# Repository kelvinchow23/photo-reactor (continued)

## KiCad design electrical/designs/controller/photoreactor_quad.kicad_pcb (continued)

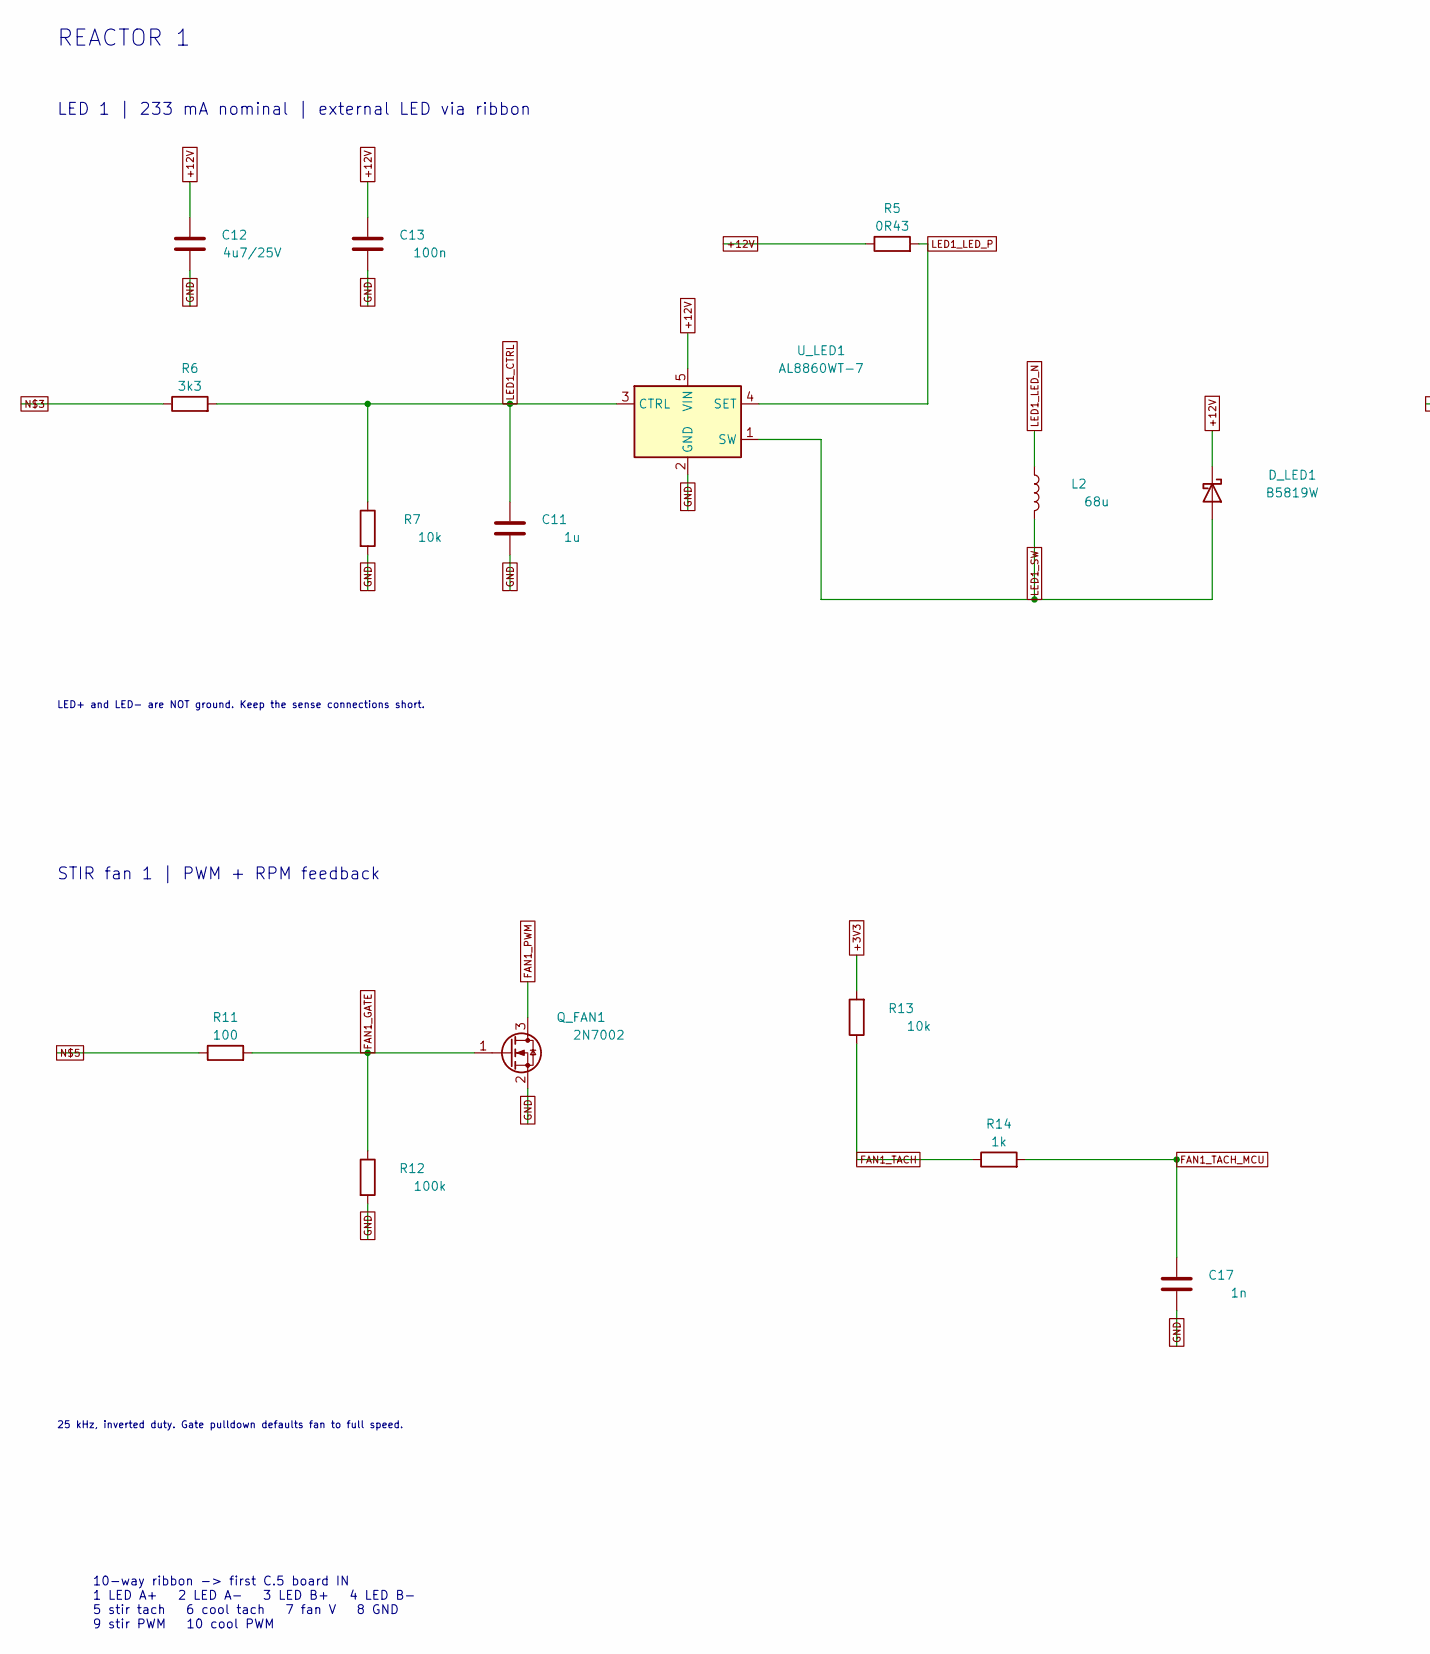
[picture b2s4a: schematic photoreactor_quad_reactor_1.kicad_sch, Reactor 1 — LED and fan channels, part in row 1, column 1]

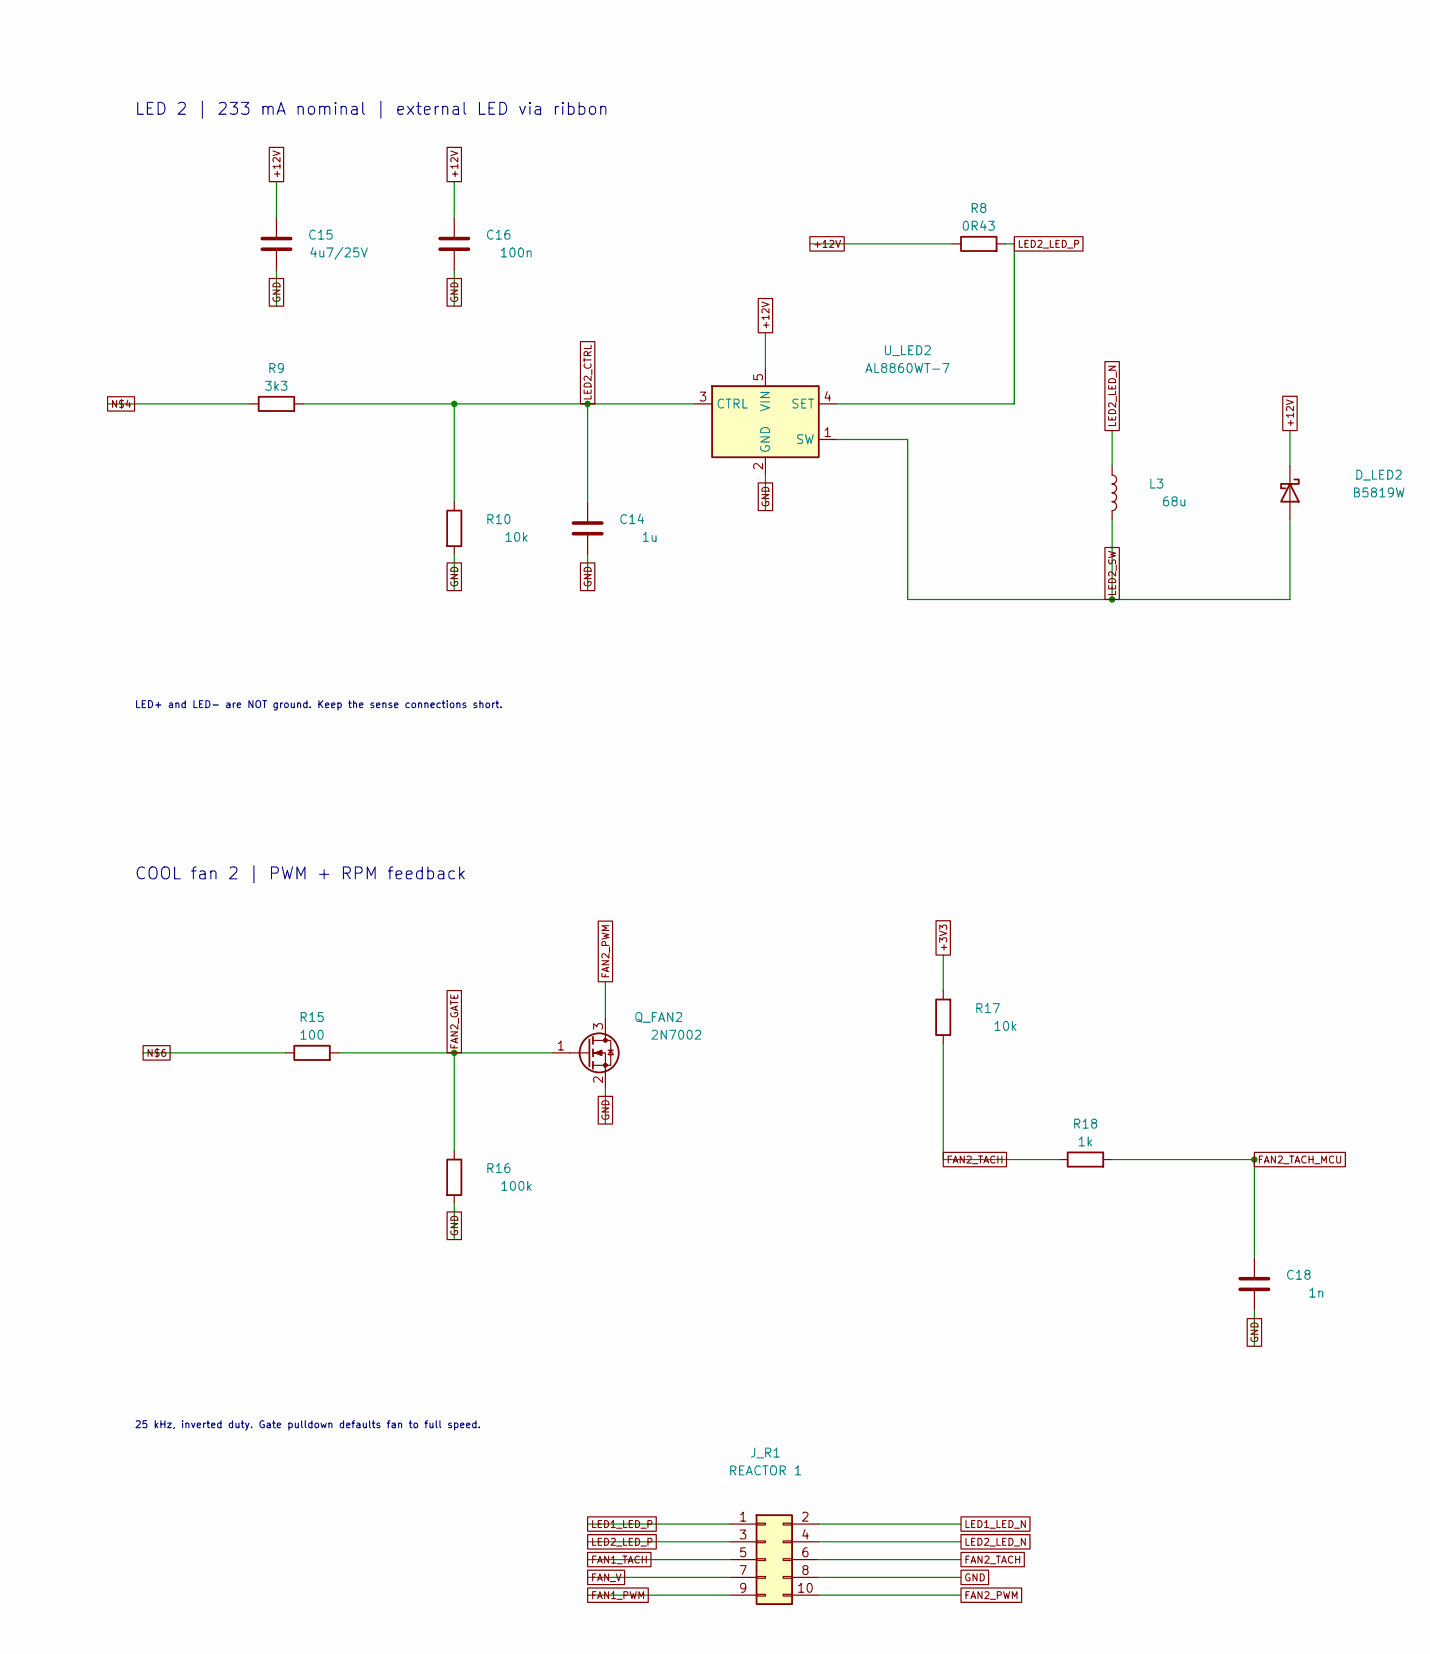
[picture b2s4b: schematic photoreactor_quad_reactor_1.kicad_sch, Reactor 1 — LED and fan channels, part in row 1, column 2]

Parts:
C11, C14: 1u; C_0805_2012Metric; MPN CL21B105KBFNNNE; LCSC C28323
C12, C15: 4u7/25V; C_0805_2012Metric; MPN CL21A475KAQNNNE; LCSC C1779
C13, C16: 100n; C_0805_2012Metric; MPN CC0805KRX7R9BB104; LCSC C49678
C17, C18: 1n; C_0805_2012Metric; MPN CL21B102KCANNNC; LCSC C15177
D_LED1, D_LED2: B5819W; D_SOD-123; MPN B5819W SL
J_R1: REACTOR 1; JXT_IDC2.54_2X5P_A2; MPN JXT-IDC2.54-2X5P-A2
L2, L3: 68u; L_Bourns_SRN6045TA; MPN SRN6045TA-680M
Q_FAN1, Q_FAN2: 2N7002; SOT-23; MPN 2N7002
R5, R8: 0R43; R_1206_3216Metric; MPN CR1206FR430P05R
R6, R9: 3k3; R_0805_2012Metric; MPN 0805W8F3301T5E; LCSC C26010
R7, R10, R13, R17: 10k; R_0805_2012Metric; MPN 0805W8F1002T5E; LCSC C17414
R11, R15: 100; R_0805_2012Metric; MPN 0805W8F1000T5E; LCSC C17408
R12, R16: 100k; R_0805_2012Metric; MPN 0805W8F1003T5E; LCSC C149504
R14, R18: 1k; R_0805_2012Metric; MPN 0805W8F1001T5E; LCSC C17513
U_LED1, U_LED2: AL8860WT-7; SOT-23-5; MPN AL8860WT-7

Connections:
+3V3: R13.2, R17.2; also elsewhere on the board
+12V: C12.1, C13.1, C15.1, C16.1, D_LED1.1 (K), D_LED2.1 (K), R5.1, R8.1, U_LED1.5 (VIN), U_LED2.5 (VIN); also elsewhere on the board
FAN1_GATE: Q_FAN1.1 (G), R11.2, R12.1
FAN1_PWM: J_R1.9, Q_FAN1.3 (D)
FAN1_TACH: J_R1.5, R13.1, R14.1
FAN1_TACH_MCU: C17.1, R14.2; also elsewhere on the board
FAN2_GATE: Q_FAN2.1 (G), R15.2, R16.1
FAN2_PWM: J_R1.10, Q_FAN2.3 (D)
FAN2_TACH: J_R1.6, R17.1, R18.1
FAN2_TACH_MCU: C18.1, R18.2; also elsewhere on the board
FAN_V: J_R1.7; also elsewhere on the board
GND: C11.2, C12.2, C13.2, C14.2, C15.2, C16.2, C17.2, C18.2, J_R1.8, Q_FAN1.2 (S), Q_FAN2.2 (S), R7.2, R10.2, R12.2, R16.2, U_LED1.2 (GND), U_LED2.2 (GND); also elsewhere on the board
LED1_CTRL: C11.1, R6.2, R7.1, U_LED1.3 (CTRL)
LED1_LED_N: J_R1.2, L2.1
LED1_LED_P: J_R1.1, R5.2, U_LED1.4 (SET)
LED1_SW: D_LED1.2 (A), L2.2, U_LED1.1 (SW)
LED2_CTRL: C14.1, R9.2, R10.1, U_LED2.3 (CTRL)
LED2_LED_N: J_R1.4, L3.1
LED2_LED_P: J_R1.3, R8.2, U_LED2.4 (SET)
LED2_SW: D_LED2.2 (A), L3.2, U_LED2.1 (SW)
unnamed 73: R6.1; also elsewhere on the board
unnamed 74: R9.1; also elsewhere on the board
unnamed 75: R11.1; also elsewhere on the board
unnamed 76: R15.1; also elsewhere on the board

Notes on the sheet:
REACTOR 1
LED 1 | 233 mA nominal | external LED via ribbon
LED+ and LED- are NOT ground. Keep the sense connections short.
LED 2 | 233 mA nominal | external LED via ribbon
STIR fan 1 | PWM + RPM feedback
25 kHz, inverted duty. Gate pulldown defaults fan to full speed.
COOL fan 2 | PWM + RPM feedback
10-way ribbon -> first C.5 board IN 1 LED A+ 2 LED A- 3 LED B+ 4 LED B- 5 stir tach 6 cool tach 7 fan V 8 GND 9 stir PWM 10 cool PWM

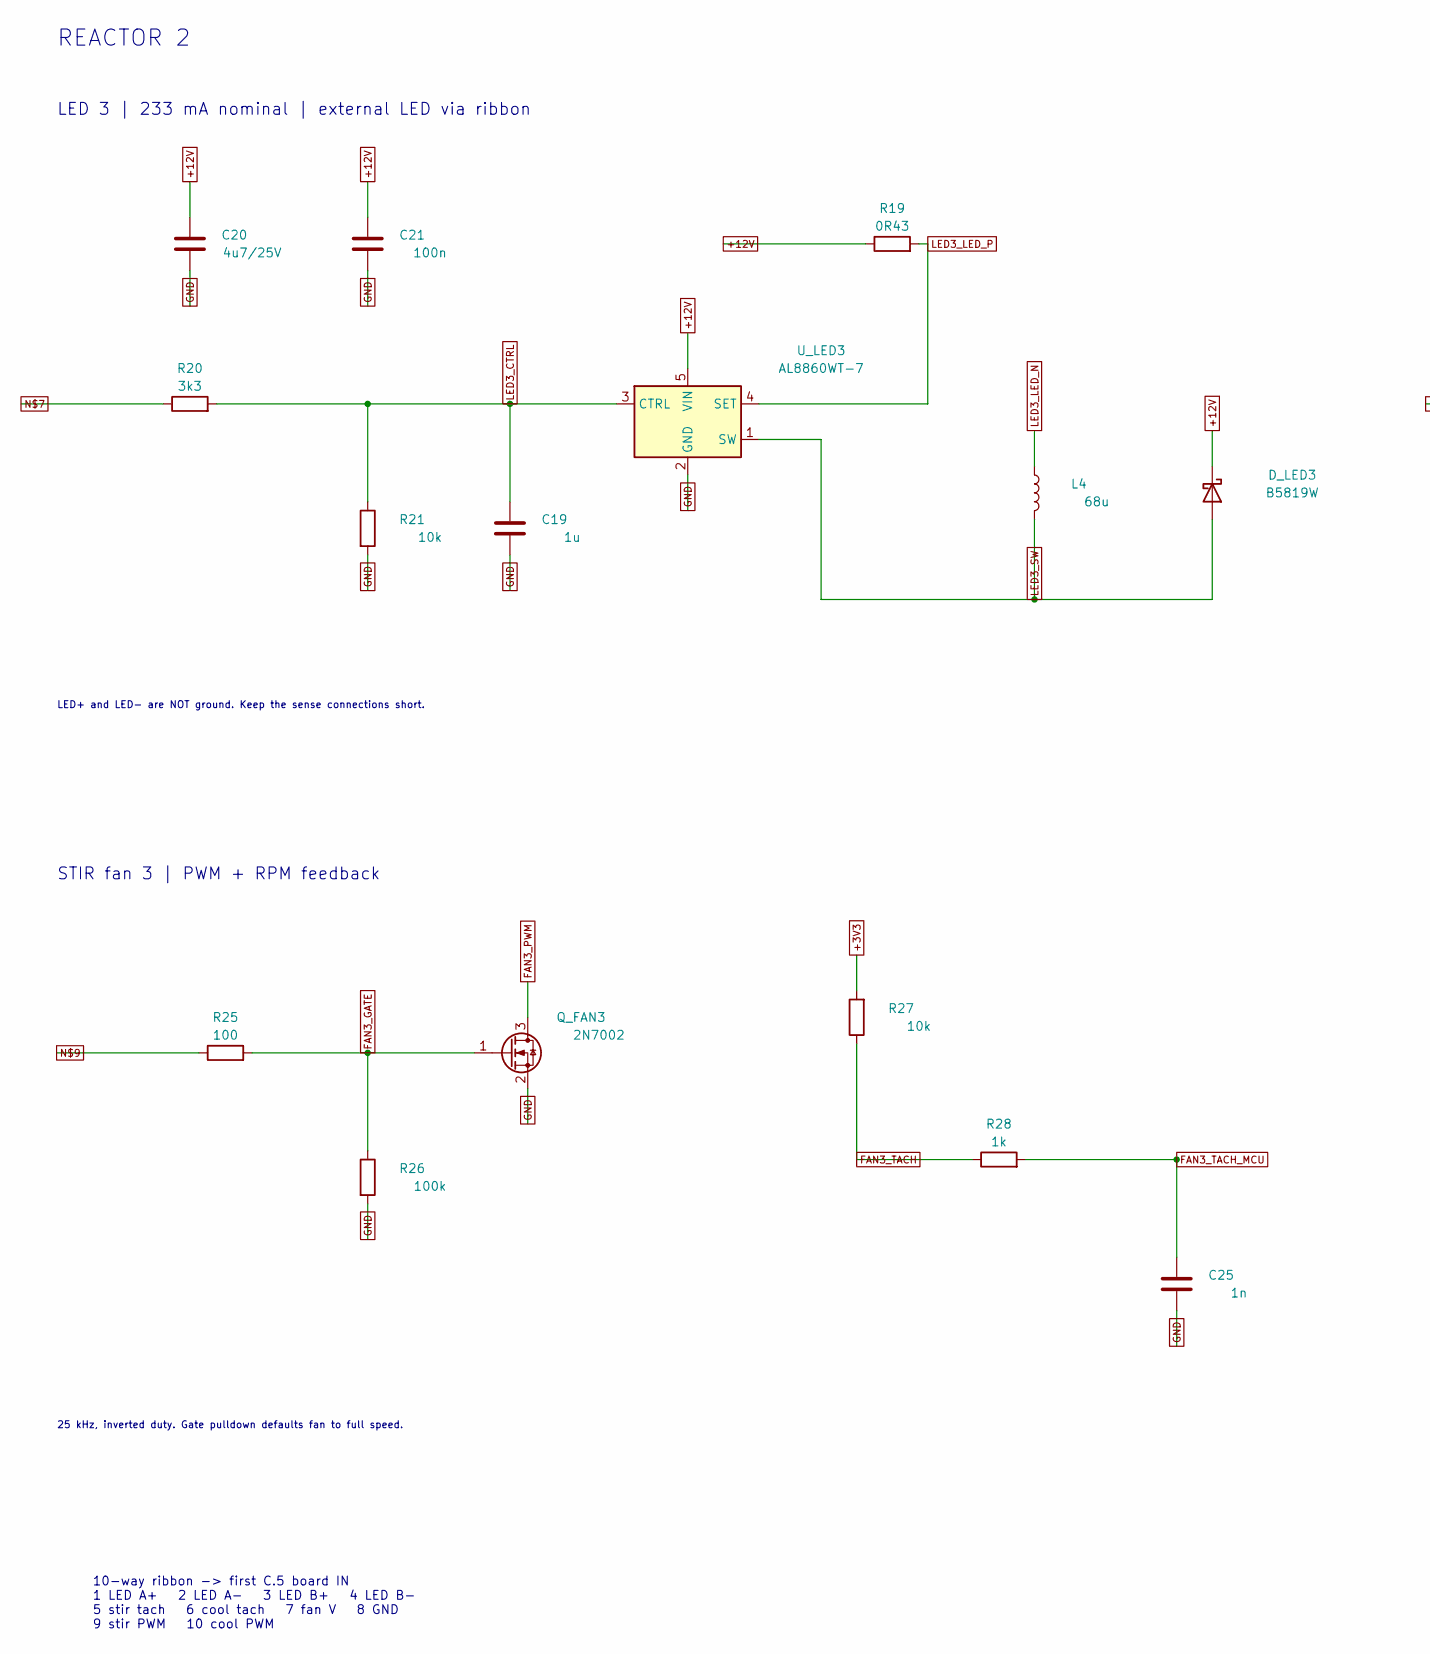
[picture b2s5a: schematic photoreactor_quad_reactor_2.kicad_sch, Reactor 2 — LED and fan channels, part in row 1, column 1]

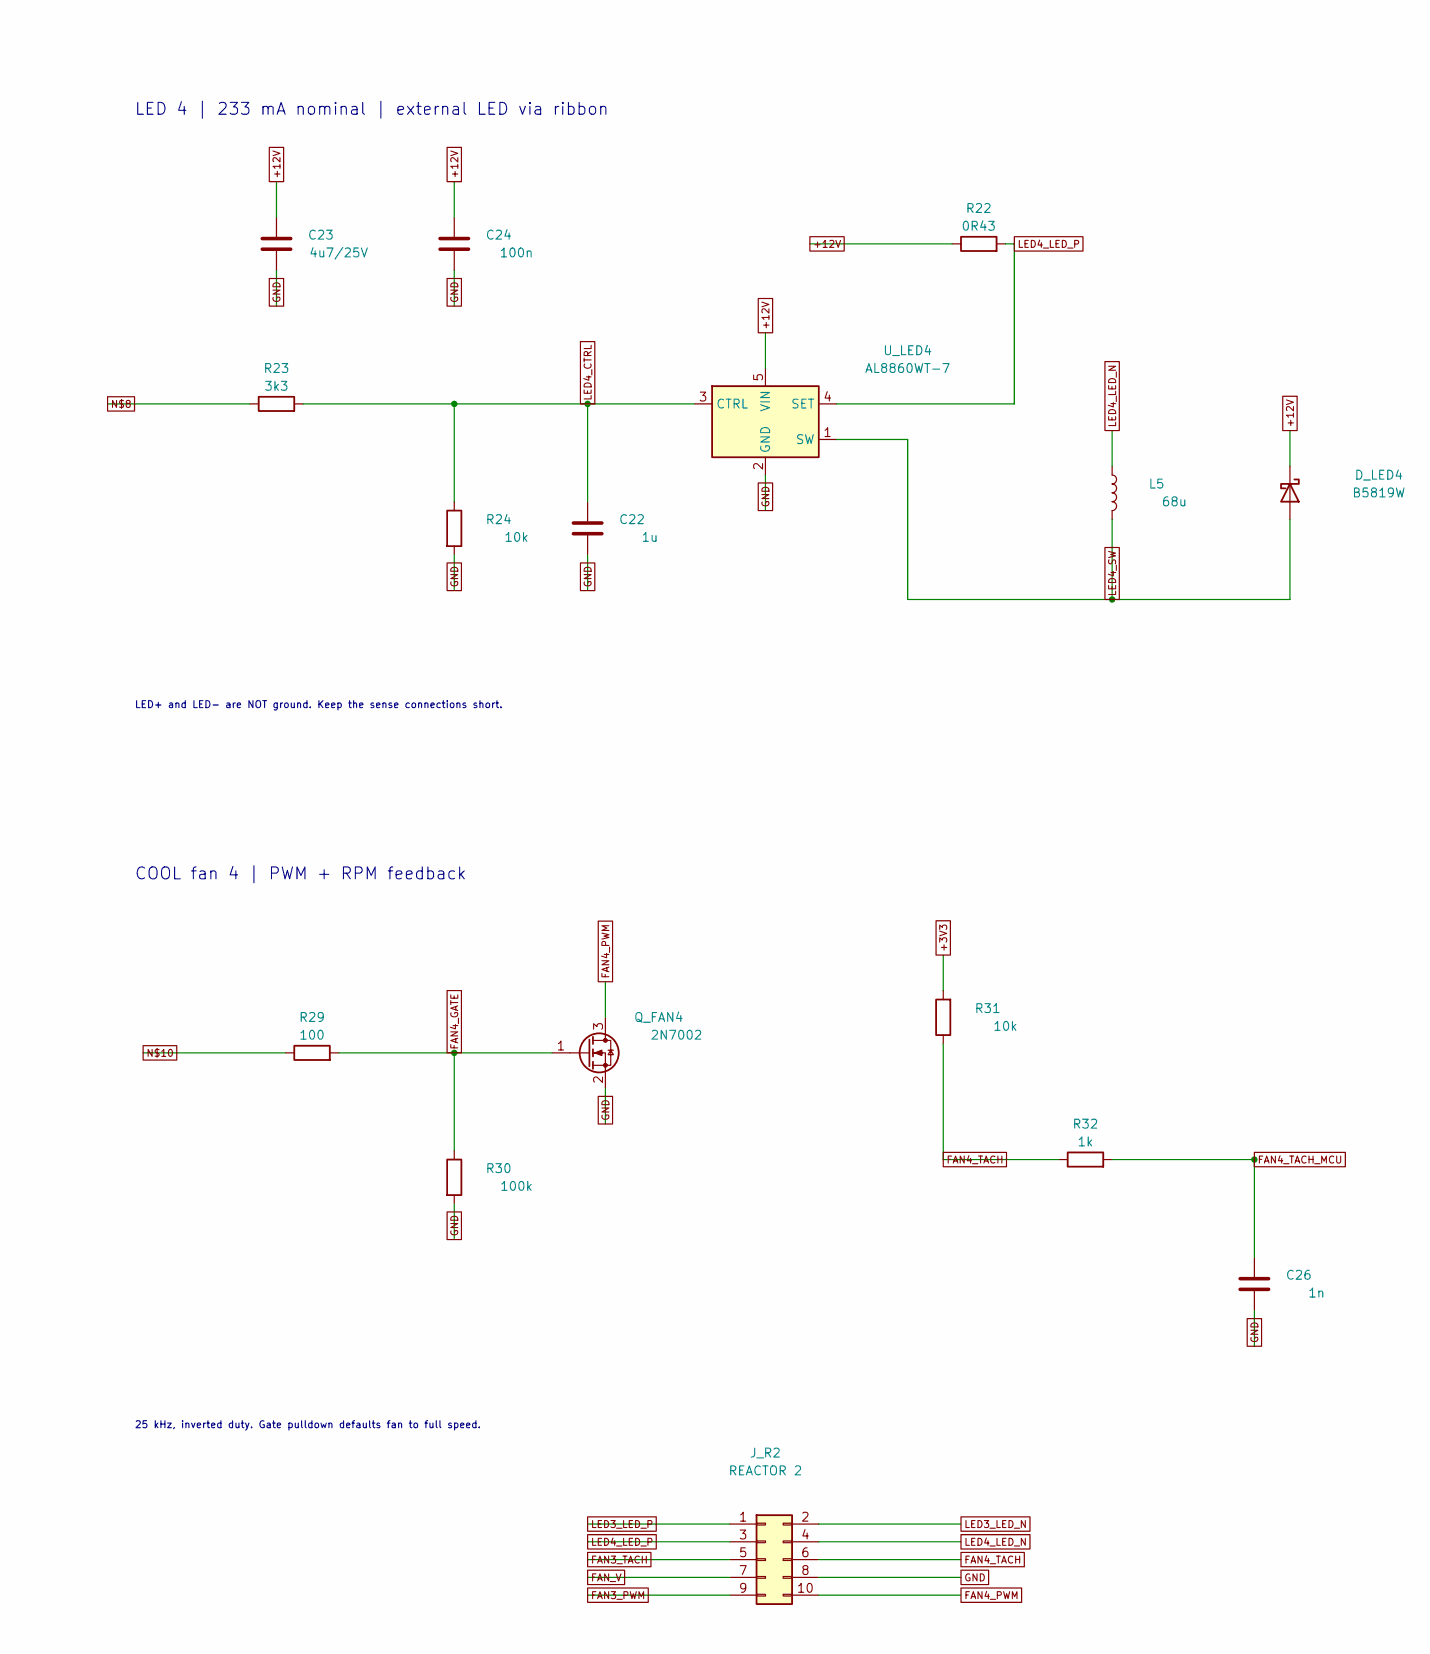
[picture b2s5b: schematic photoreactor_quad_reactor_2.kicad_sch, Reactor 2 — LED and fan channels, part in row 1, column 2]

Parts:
C19, C22: 1u; C_0805_2012Metric; MPN CL21B105KBFNNNE; LCSC C28323
C20, C23: 4u7/25V; C_0805_2012Metric; MPN CL21A475KAQNNNE; LCSC C1779
C21, C24: 100n; C_0805_2012Metric; MPN CC0805KRX7R9BB104; LCSC C49678
C25, C26: 1n; C_0805_2012Metric; MPN CL21B102KCANNNC; LCSC C15177
D_LED3, D_LED4: B5819W; D_SOD-123; MPN B5819W SL
J_R2: REACTOR 2; JXT_IDC2.54_2X5P_A2; MPN JXT-IDC2.54-2X5P-A2
L4, L5: 68u; L_Bourns_SRN6045TA; MPN SRN6045TA-680M
Q_FAN3, Q_FAN4: 2N7002; SOT-23; MPN 2N7002
R19, R22: 0R43; R_1206_3216Metric; MPN CR1206FR430P05R
R20, R23: 3k3; R_0805_2012Metric; MPN 0805W8F3301T5E; LCSC C26010
R21, R24, R27, R31: 10k; R_0805_2012Metric; MPN 0805W8F1002T5E; LCSC C17414
R25, R29: 100; R_0805_2012Metric; MPN 0805W8F1000T5E; LCSC C17408
R26, R30: 100k; R_0805_2012Metric; MPN 0805W8F1003T5E; LCSC C149504
R28, R32: 1k; R_0805_2012Metric; MPN 0805W8F1001T5E; LCSC C17513
U_LED3, U_LED4: AL8860WT-7; SOT-23-5; MPN AL8860WT-7

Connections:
+3V3: R27.2, R31.2; also elsewhere on the board
+12V: C20.1, C21.1, C23.1, C24.1, D_LED3.1 (K), D_LED4.1 (K), R19.1, R22.1, U_LED3.5 (VIN), U_LED4.5 (VIN); also elsewhere on the board
FAN3_GATE: Q_FAN3.1 (G), R25.2, R26.1
FAN3_PWM: J_R2.9, Q_FAN3.3 (D)
FAN3_TACH: J_R2.5, R27.1, R28.1
FAN3_TACH_MCU: C25.1, R28.2; also elsewhere on the board
FAN4_GATE: Q_FAN4.1 (G), R29.2, R30.1
FAN4_PWM: J_R2.10, Q_FAN4.3 (D)
FAN4_TACH: J_R2.6, R31.1, R32.1
FAN4_TACH_MCU: C26.1, R32.2; also elsewhere on the board
FAN_V: J_R2.7; also elsewhere on the board
GND: C19.2, C20.2, C21.2, C22.2, C23.2, C24.2, C25.2, C26.2, J_R2.8, Q_FAN3.2 (S), Q_FAN4.2 (S), R21.2, R24.2, R26.2, R30.2, U_LED3.2 (GND), U_LED4.2 (GND); also elsewhere on the board
LED3_CTRL: C19.1, R20.2, R21.1, U_LED3.3 (CTRL)
LED3_LED_N: J_R2.2, L4.1
LED3_LED_P: J_R2.1, R19.2, U_LED3.4 (SET)
LED3_SW: D_LED3.2 (A), L4.2, U_LED3.1 (SW)
LED4_CTRL: C22.1, R23.2, R24.1, U_LED4.3 (CTRL)
LED4_LED_N: J_R2.4, L5.1
LED4_LED_P: J_R2.3, R22.2, U_LED4.4 (SET)
LED4_SW: D_LED4.2 (A), L5.2, U_LED4.1 (SW)
unnamed 77: R20.1; also elsewhere on the board
unnamed 78: R23.1; also elsewhere on the board
unnamed 79: R25.1; also elsewhere on the board
unnamed 80: R29.1; also elsewhere on the board

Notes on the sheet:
REACTOR 2
LED 3 | 233 mA nominal | external LED via ribbon
LED+ and LED- are NOT ground. Keep the sense connections short.
LED 4 | 233 mA nominal | external LED via ribbon
STIR fan 3 | PWM + RPM feedback
25 kHz, inverted duty. Gate pulldown defaults fan to full speed.
COOL fan 4 | PWM + RPM feedback
10-way ribbon -> first C.5 board IN 1 LED A+ 2 LED A- 3 LED B+ 4 LED B- 5 stir tach 6 cool tach 7 fan V 8 GND 9 stir PWM 10 cool PWM

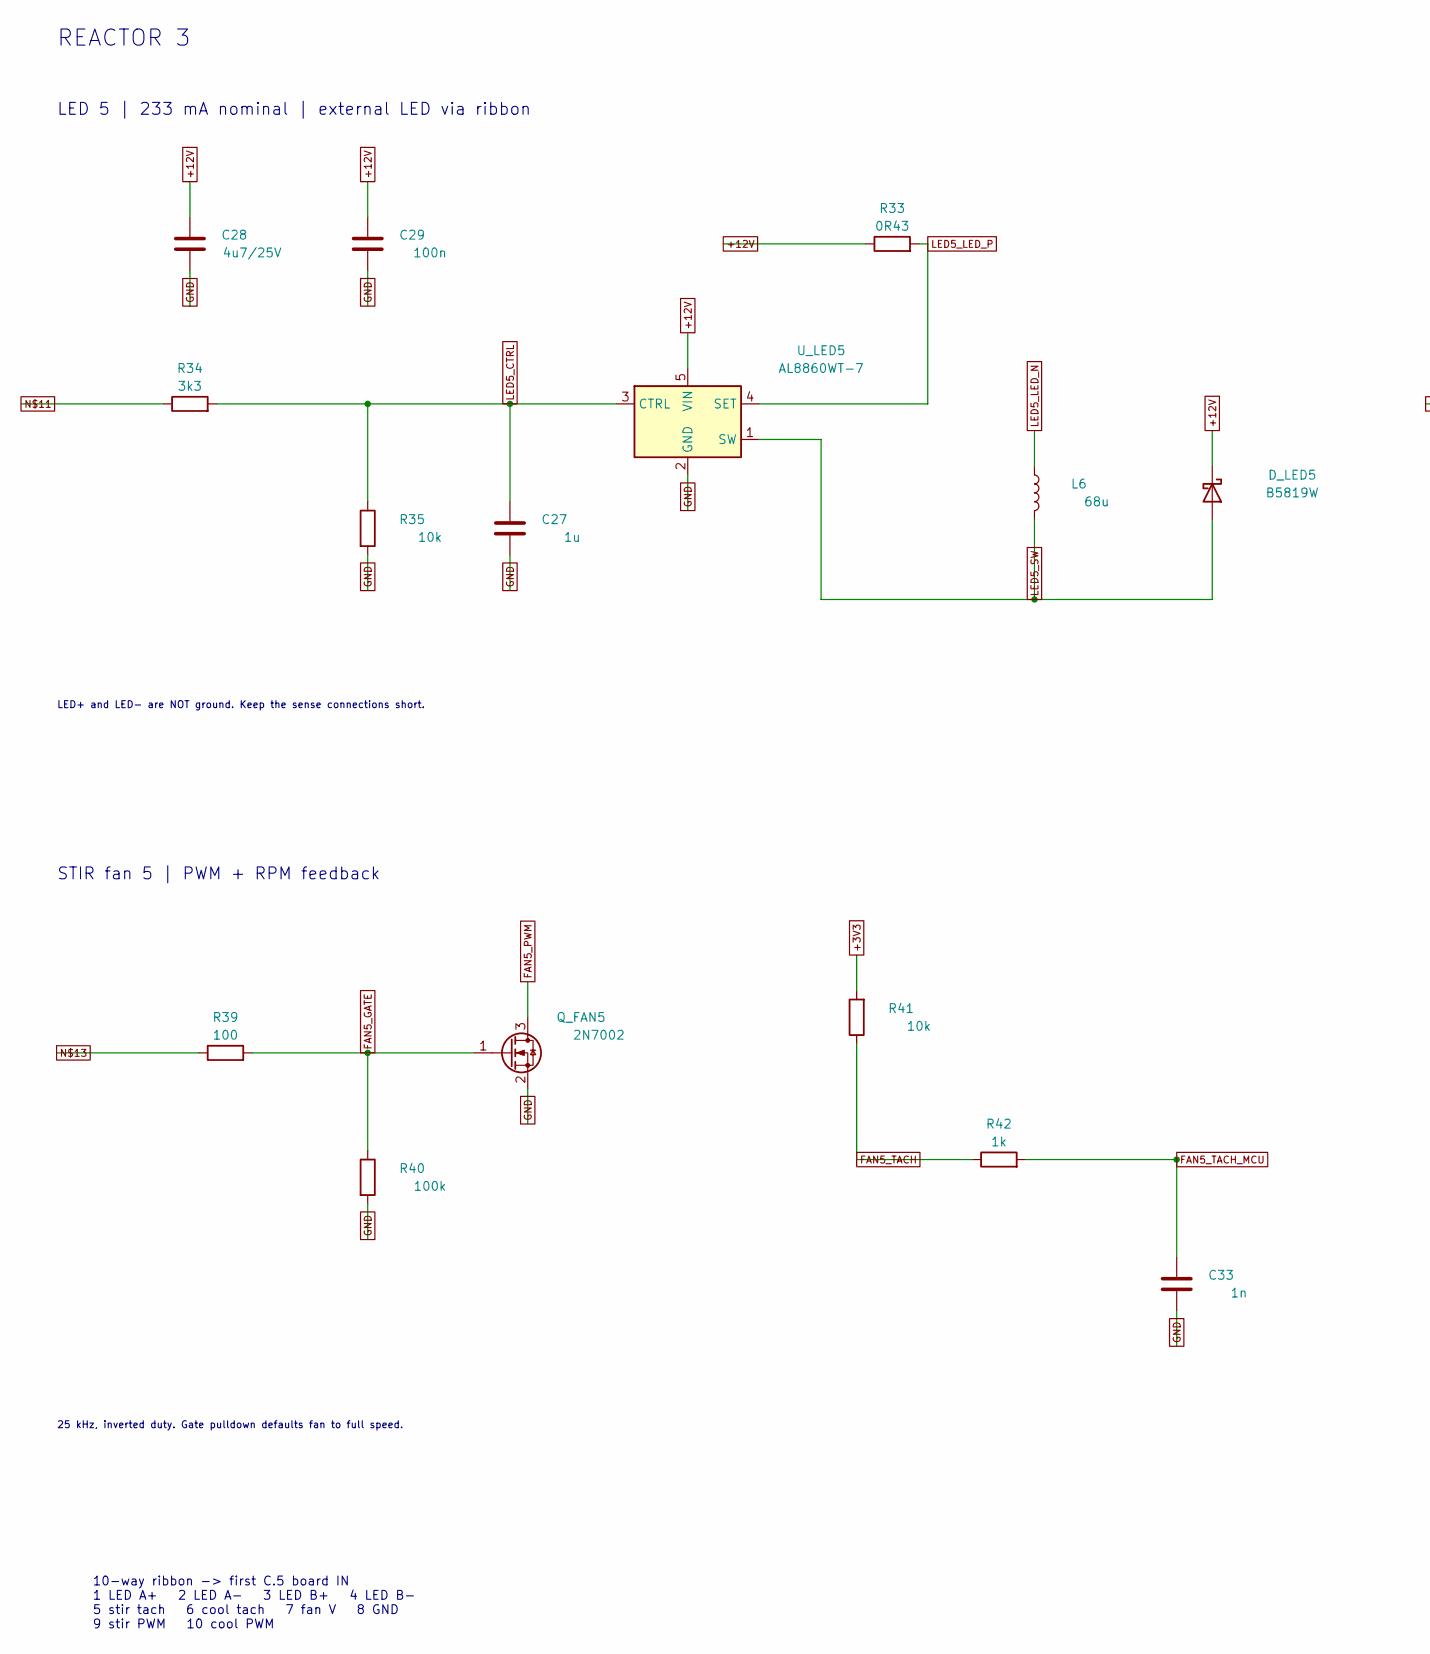
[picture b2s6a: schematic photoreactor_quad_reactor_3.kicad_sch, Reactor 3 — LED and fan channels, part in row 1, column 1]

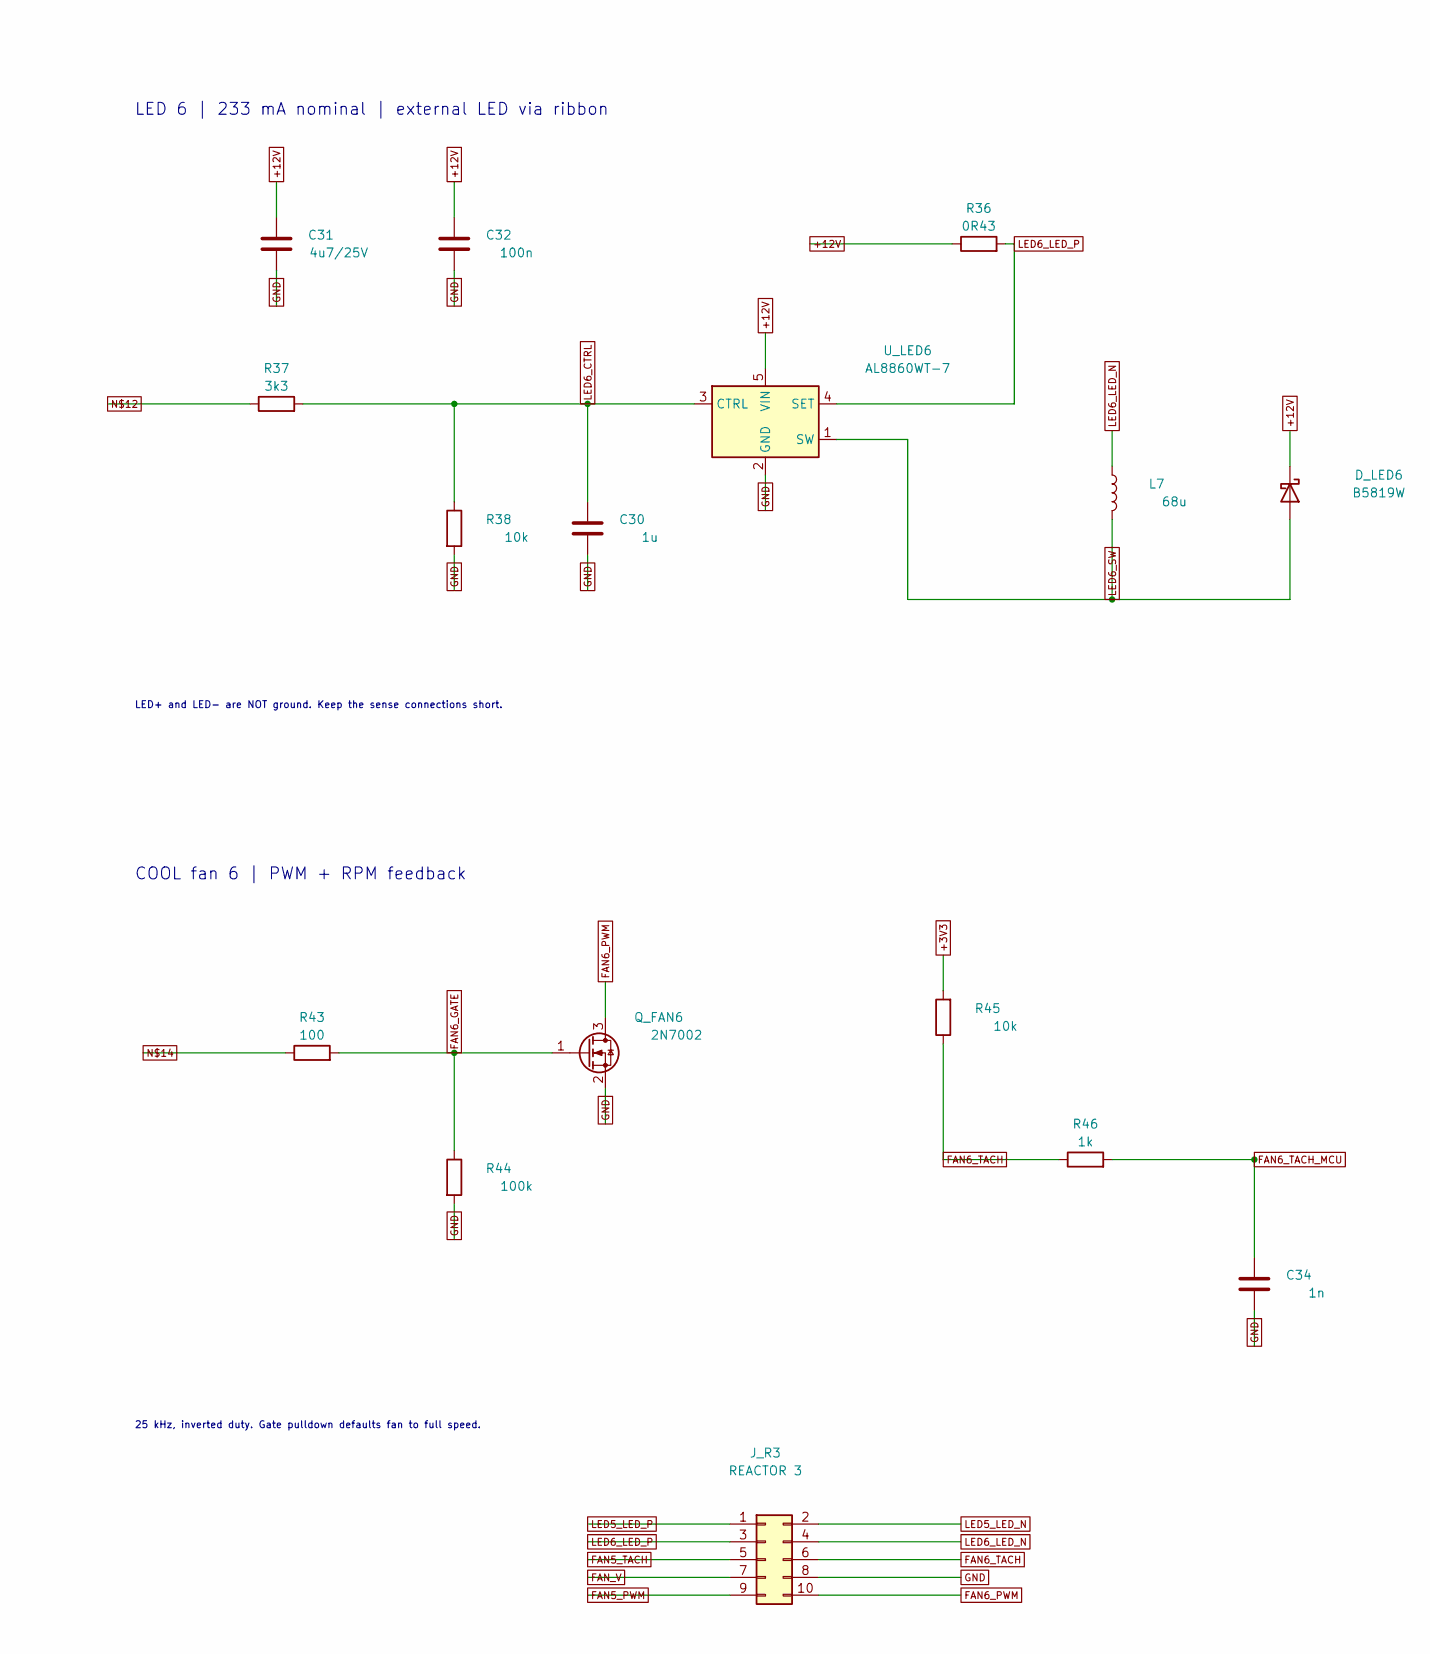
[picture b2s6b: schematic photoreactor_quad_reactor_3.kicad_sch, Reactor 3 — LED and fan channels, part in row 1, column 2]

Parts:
C27, C30: 1u; C_0805_2012Metric; MPN CL21B105KBFNNNE; LCSC C28323
C28, C31: 4u7/25V; C_0805_2012Metric; MPN CL21A475KAQNNNE; LCSC C1779
C29, C32: 100n; C_0805_2012Metric; MPN CC0805KRX7R9BB104; LCSC C49678
C33, C34: 1n; C_0805_2012Metric; MPN CL21B102KCANNNC; LCSC C15177
D_LED5, D_LED6: B5819W; D_SOD-123; MPN B5819W SL
J_R3: REACTOR 3; JXT_IDC2.54_2X5P_A2; MPN JXT-IDC2.54-2X5P-A2
L6, L7: 68u; L_Bourns_SRN6045TA; MPN SRN6045TA-680M
Q_FAN5, Q_FAN6: 2N7002; SOT-23; MPN 2N7002
R33, R36: 0R43; R_1206_3216Metric; MPN CR1206FR430P05R
R34, R37: 3k3; R_0805_2012Metric; MPN 0805W8F3301T5E; LCSC C26010
R35, R38, R41, R45: 10k; R_0805_2012Metric; MPN 0805W8F1002T5E; LCSC C17414
R39, R43: 100; R_0805_2012Metric; MPN 0805W8F1000T5E; LCSC C17408
R40, R44: 100k; R_0805_2012Metric; MPN 0805W8F1003T5E; LCSC C149504
R42, R46: 1k; R_0805_2012Metric; MPN 0805W8F1001T5E; LCSC C17513
U_LED5, U_LED6: AL8860WT-7; SOT-23-5; MPN AL8860WT-7

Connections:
+3V3: R41.2, R45.2; also elsewhere on the board
+12V: C28.1, C29.1, C31.1, C32.1, D_LED5.1 (K), D_LED6.1 (K), R33.1, R36.1, U_LED5.5 (VIN), U_LED6.5 (VIN); also elsewhere on the board
FAN5_GATE: Q_FAN5.1 (G), R39.2, R40.1
FAN5_PWM: J_R3.9, Q_FAN5.3 (D)
FAN5_TACH: J_R3.5, R41.1, R42.1
FAN5_TACH_MCU: C33.1, R42.2; also elsewhere on the board
FAN6_GATE: Q_FAN6.1 (G), R43.2, R44.1
FAN6_PWM: J_R3.10, Q_FAN6.3 (D)
FAN6_TACH: J_R3.6, R45.1, R46.1
FAN6_TACH_MCU: C34.1, R46.2; also elsewhere on the board
FAN_V: J_R3.7; also elsewhere on the board
GND: C27.2, C28.2, C29.2, C30.2, C31.2, C32.2, C33.2, C34.2, J_R3.8, Q_FAN5.2 (S), Q_FAN6.2 (S), R35.2, R38.2, R40.2, R44.2, U_LED5.2 (GND), U_LED6.2 (GND); also elsewhere on the board
LED5_CTRL: C27.1, R34.2, R35.1, U_LED5.3 (CTRL)
LED5_LED_N: J_R3.2, L6.1
LED5_LED_P: J_R3.1, R33.2, U_LED5.4 (SET)
LED5_SW: D_LED5.2 (A), L6.2, U_LED5.1 (SW)
LED6_CTRL: C30.1, R37.2, R38.1, U_LED6.3 (CTRL)
LED6_LED_N: J_R3.4, L7.1
LED6_LED_P: J_R3.3, R36.2, U_LED6.4 (SET)
LED6_SW: D_LED6.2 (A), L7.2, U_LED6.1 (SW)
unnamed 81: R34.1; also elsewhere on the board
unnamed 82: R37.1; also elsewhere on the board
unnamed 83: R39.1; also elsewhere on the board
unnamed 84: R43.1; also elsewhere on the board

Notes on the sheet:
REACTOR 3
LED 5 | 233 mA nominal | external LED via ribbon
LED+ and LED- are NOT ground. Keep the sense connections short.
LED 6 | 233 mA nominal | external LED via ribbon
STIR fan 5 | PWM + RPM feedback
25 kHz, inverted duty. Gate pulldown defaults fan to full speed.
COOL fan 6 | PWM + RPM feedback
10-way ribbon -> first C.5 board IN 1 LED A+ 2 LED A- 3 LED B+ 4 LED B- 5 stir tach 6 cool tach 7 fan V 8 GND 9 stir PWM 10 cool PWM
